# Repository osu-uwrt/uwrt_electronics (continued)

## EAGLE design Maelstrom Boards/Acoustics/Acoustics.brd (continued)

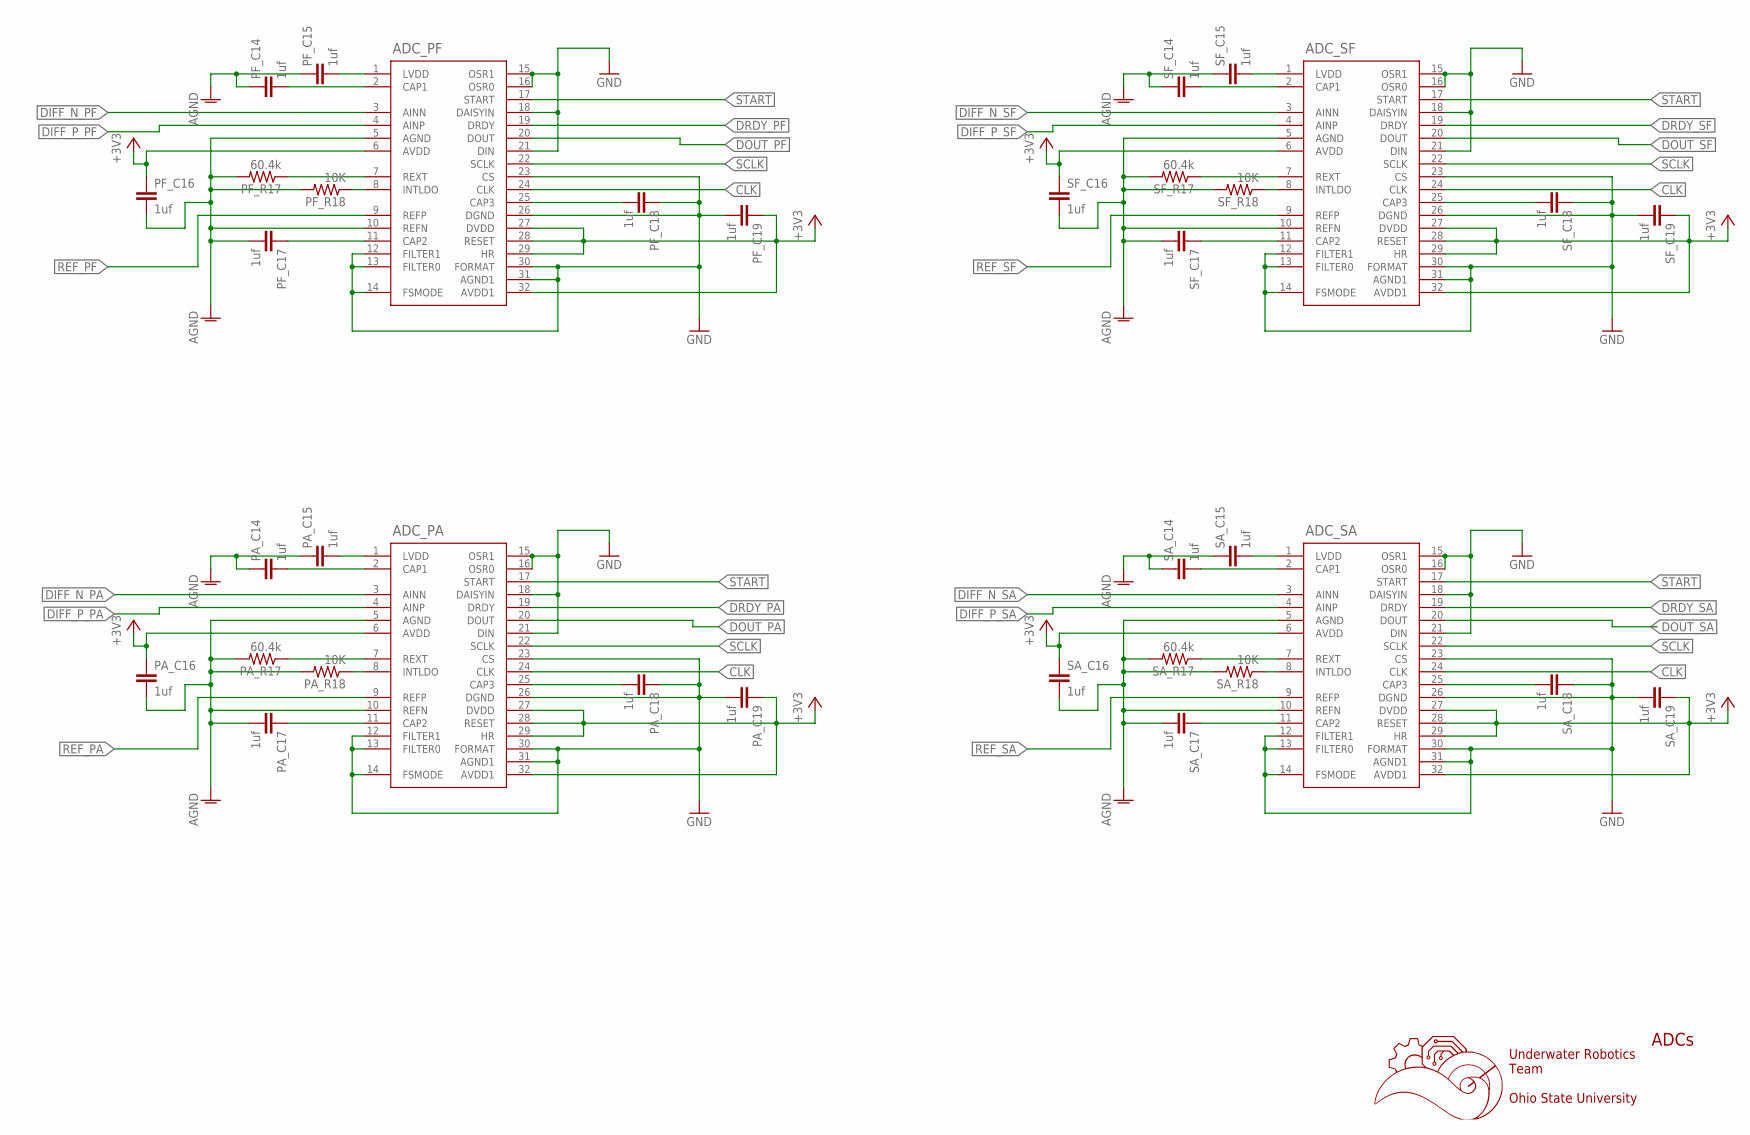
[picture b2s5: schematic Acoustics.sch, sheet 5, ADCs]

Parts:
ADC_PA: ADS124S08IPBSRPBS0032A_L; PBS0032A_L
ADC_PF: ADS124S08IPBSRPBS0032A_L; PBS0032A_L
ADC_SA: ADS124S08IPBSRPBS0032A_L; PBS0032A_L
ADC_SF: ADS124S08IPBSRPBS0032A_L; PBS0032A_L
PA_C14, PA_C15, PA_C17, PA_C18, PA_C19: 1uf; C0603
PA_C16: 1uf; C0603K
PA_R17: 60.4k; R0603
PA_R18: 10K; R0603
PF_C14, PF_C15, PF_C17, PF_C18, PF_C19: 1uf; C0603
PF_C16: 1uf; C0603K
PF_R17: 60.4k; R0603
PF_R18: 10K; R0603
SA_C14, SA_C15, SA_C17, SA_C18, SA_C19: 1uf; C0603
SA_C16: 1uf; C0603K
SA_R17: 60.4k; R0603
SA_R18: 10K; R0603
SF_C14, SF_C15, SF_C17, SF_C18, SF_C19: 1uf; C0603
SF_C16: 1uf; C0603K
SF_R17: 60.4k; R0603
SF_R18: 10K; R0603

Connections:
+3V3: ADC_PA.6 (AVDD), ADC_PA.27 (DVDD), ADC_PA.28 (RESET), ADC_PA.29 (HR), ADC_PA.32 (AVDD1), ADC_PF.6 (AVDD), ADC_PF.27 (DVDD), ADC_PF.28 (RESET), ADC_PF.29 (HR), ADC_PF.32 (AVDD1), ADC_SA.6 (AVDD), ADC_SA.27 (DVDD), ADC_SA.28 (RESET), ADC_SA.29 (HR), ADC_SA.32 (AVDD1), ADC_SF.6 (AVDD), ADC_SF.27 (DVDD), ADC_SF.28 (RESET), ADC_SF.29 (HR), ADC_SF.32 (AVDD1), PA_C16.1, PA_C19.1, PF_C16.1, PF_C19.1, SA_C16.1, SA_C19.1, SF_C16.1, SF_C19.1; also elsewhere on the board
CLK: ADC_PA.24 (CLK), ADC_PF.24 (CLK), ADC_SA.24 (CLK), ADC_SF.24 (CLK); also elsewhere on the board
DIFF_N_PA: ADC_PA.3 (AINN); also elsewhere on the board
DIFF_N_PF: ADC_PF.3 (AINN); also elsewhere on the board
DIFF_N_SA: ADC_SA.3 (AINN); also elsewhere on the board
DIFF_N_SF: ADC_SF.3 (AINN); also elsewhere on the board
DIFF_P_PA: ADC_PA.4 (AINP); also elsewhere on the board
DIFF_P_PF: ADC_PF.4 (AINP); also elsewhere on the board
DIFF_P_SA: ADC_SA.4 (AINP); also elsewhere on the board
DIFF_P_SF: ADC_SF.4 (AINP); also elsewhere on the board
DOUT_PA: ADC_PA.20 (DOUT); also elsewhere on the board
DOUT_PF: ADC_PF.20 (DOUT); also elsewhere on the board
DOUT_SA: ADC_SA.20 (DOUT); also elsewhere on the board
DOUT_SF: ADC_SF.20 (DOUT); also elsewhere on the board
DRDY_PA: ADC_PA.19 (DRDY); also elsewhere on the board
DRDY_PF: ADC_PF.19 (DRDY); also elsewhere on the board
DRDY_SA: ADC_SA.19 (DRDY); also elsewhere on the board
DRDY_SF: ADC_SF.19 (DRDY); also elsewhere on the board
GND: ADC_PA.5 (AGND), ADC_PA.10 (REFN), ADC_PA.12 (FILTER1), ADC_PA.13 (FILTER0), ADC_PA.14 (FSMODE), ADC_PA.15 (OSR1), ADC_PA.16 (OSR0), ADC_PA.18 (DAISYIN), ADC_PA.21 (DIN), ADC_PA.23 (CS), ADC_PA.26 (DGND), ADC_PA.30 (FORMAT), ADC_PA.31 (AGND1), ADC_PF.5 (AGND), ADC_PF.10 (REFN), ADC_PF.12 (FILTER1), ADC_PF.13 (FILTER0), ADC_PF.14 (FSMODE), ADC_PF.15 (OSR1), ADC_PF.16 (OSR0), ADC_PF.18 (DAISYIN), ADC_PF.21 (DIN), ADC_PF.23 (CS), ADC_PF.26 (DGND), ADC_PF.30 (FORMAT), ADC_PF.31 (AGND1), ADC_SA.5 (AGND), ADC_SA.10 (REFN), ADC_SA.12 (FILTER1), ADC_SA.13 (FILTER0), ADC_SA.14 (FSMODE), ADC_SA.15 (OSR1), ADC_SA.16 (OSR0), ADC_SA.18 (DAISYIN), ADC_SA.21 (DIN), ADC_SA.23 (CS), ADC_SA.26 (DGND), ADC_SA.30 (FORMAT), ADC_SA.31 (AGND1), ADC_SF.5 (AGND), ADC_SF.10 (REFN), ADC_SF.12 (FILTER1), ADC_SF.13 (FILTER0), ADC_SF.14 (FSMODE), ADC_SF.15 (OSR1), ADC_SF.16 (OSR0), ADC_SF.18 (DAISYIN), ADC_SF.21 (DIN), ADC_SF.23 (CS), ADC_SF.26 (DGND), ADC_SF.30 (FORMAT), ADC_SF.31 (AGND1), PA_C14.1, PA_C15.1, PA_C16.2, PA_C17.2, PA_C18.1, PA_C19.2, PA_R17.2, PA_R18.2, PF_C14.1, PF_C15.1, PF_C16.2, PF_C17.2, PF_C18.1, PF_C19.2, PF_R17.2, PF_R18.2, SA_C14.1, SA_C15.1, SA_C16.2, SA_C17.2, SA_C18.1, SA_C19.2, SA_R17.2, SA_R18.2, SF_C14.1, SF_C15.1, SF_C16.2, SF_C17.2, SF_C18.1, SF_C19.2, SF_R17.2, SF_R18.2; also elsewhere on the board
unnamed: ADC_PF.2 (CAP1), PF_C14.2
unnamed: ADC_PA.1 (LVDD), PA_C15.2
unnamed: ADC_PA.8 (INTLDO), PA_R18.1
unnamed: ADC_PA.7 (REXT), PA_R17.1
unnamed: ADC_PA.11 (CAP2), PA_C17.1
unnamed: ADC_PA.25 (CAP3), PA_C18.2
unnamed: ADC_PF.1 (LVDD), PF_C15.2
unnamed: ADC_PA.2 (CAP1), PA_C14.2
unnamed: ADC_PF.8 (INTLDO), PF_R18.1
unnamed: ADC_PF.7 (REXT), PF_R17.1
unnamed: ADC_PF.11 (CAP2), PF_C17.1
unnamed: ADC_PF.25 (CAP3), PF_C18.2
unnamed: ADC_SF.1 (LVDD), SF_C15.2
unnamed: ADC_SF.8 (INTLDO), SF_R18.1
unnamed: ADC_SF.7 (REXT), SF_R17.1
unnamed: ADC_SF.11 (CAP2), SF_C17.1
unnamed: ADC_SF.25 (CAP3), SF_C18.2
unnamed: ADC_SF.2 (CAP1), SF_C14.2
unnamed: ADC_SA.1 (LVDD), SA_C15.2
unnamed: ADC_SA.8 (INTLDO), SA_R18.1
unnamed: ADC_SA.7 (REXT), SA_R17.1
unnamed: ADC_SA.11 (CAP2), SA_C17.1
unnamed: ADC_SA.25 (CAP3), SA_C18.2
unnamed: ADC_SA.2 (CAP1), SA_C14.2
REF_PA: ADC_PA.9 (REFP); also elsewhere on the board
REF_PF: ADC_PF.9 (REFP); also elsewhere on the board
REF_SA: ADC_SA.9 (REFP); also elsewhere on the board
REF_SF: ADC_SF.9 (REFP); also elsewhere on the board
SCLK: ADC_PA.22 (SCLK), ADC_PF.22 (SCLK), ADC_SA.22 (SCLK), ADC_SF.22 (SCLK); also elsewhere on the board
START: ADC_PA.17 (START), ADC_PF.17 (START), ADC_SA.17 (START), ADC_SF.17 (START); also elsewhere on the board

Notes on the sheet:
Underwater Robotics Team Ohio State University
ADCs

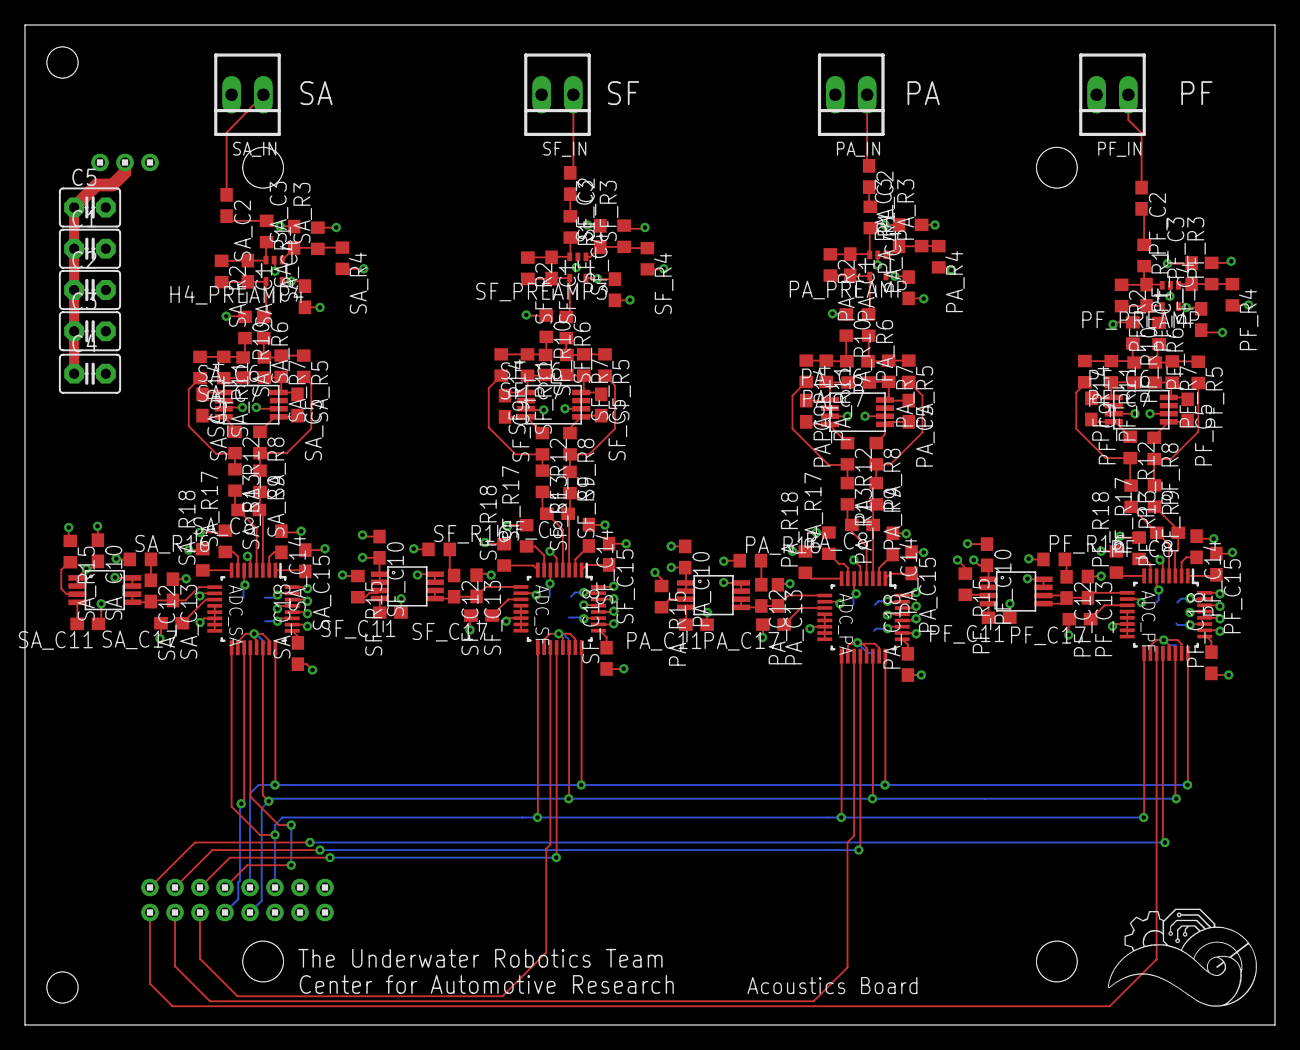
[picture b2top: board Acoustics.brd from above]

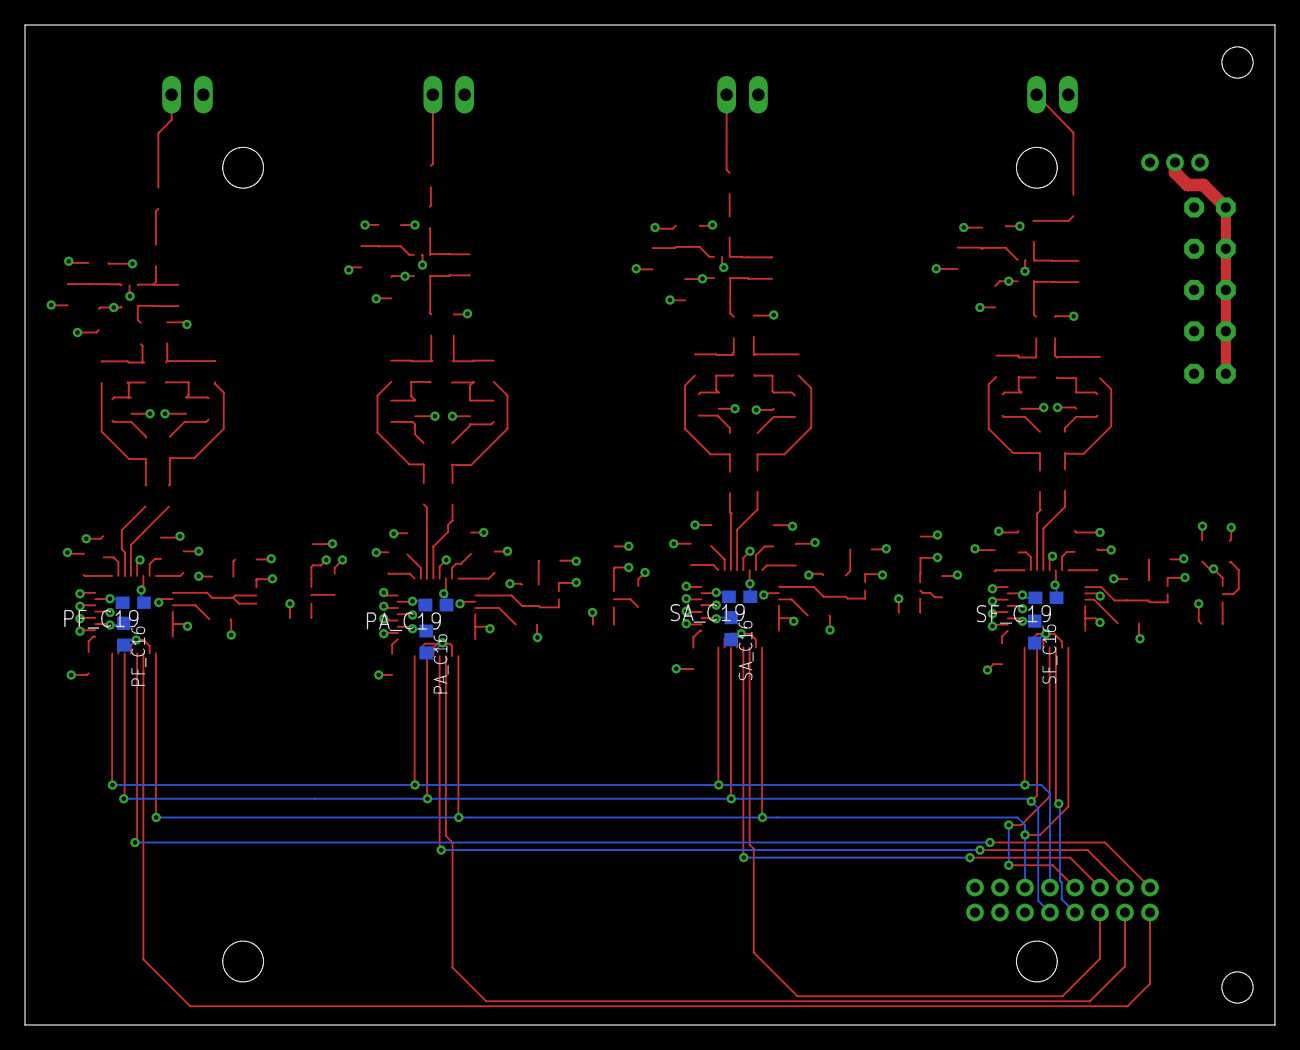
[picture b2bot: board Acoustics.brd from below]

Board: 4 copper layers, 100.0 x 80.0 mm, 175 parts (8 on the bottom side), 114 nets.

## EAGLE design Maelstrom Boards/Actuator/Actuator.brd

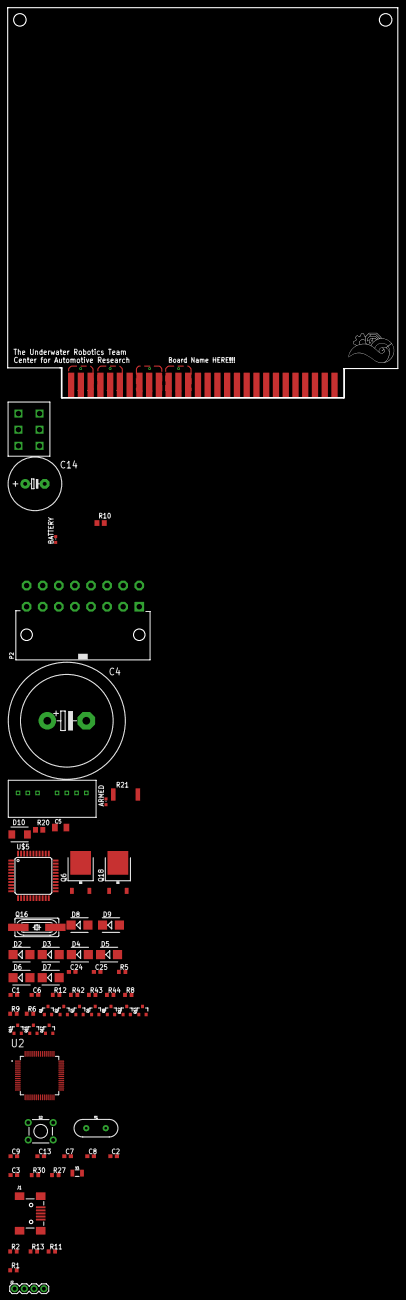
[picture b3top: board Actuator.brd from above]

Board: 2 copper layers, 101.6 x 101.6 mm, 65 parts (0 on the bottom side), 57 nets, no tracks yet.

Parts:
ARMED: CHIPLED_0603
BATTERY: CHIPLED_0603
C1, C6: 30pF; C0603
C2, C3: 18pF; C0603
C4: 22mF; EB30D
C5: 47 uF; C1206K
C7, C8: 2.2uF; C0603
C9, C13: 12.5pF; C0603
C14: 1000 uF; E5-13
C24: 220nF; C0603
C25: 100nF; C0603
D2, D3, D4, D5, D6, D7, D8, D9: SMB
D10: SMBJ
J1: USB_MINI-B_SMT; USB-MINIB
J2: 1X04
P2: 39-30-16?; 39-30-?16?
Q1, Q2, Q3, Q4, Q5, Q12, Q13, Q14, Q15, Q17: SOT23-3
Q6, Q18: TO252
Q16: HC49UP
R1, R13: 22; R0603
R2, R30: 100k; R0603
R5: 100K; R0603
R6: 5; R0603
R8, R42: 10K; R0603
R9, R12, R43, R44: 10k; R0603
R10, R20: 1.2k; R0805
R11: 560; R0603
R21: 120; R6332W
R27: 4.7k; R0603
S2: MOMENTARY-SWITCH-SPST-PTH-6.0MM; TACTILE_SWITCH_PTH_6.0MM
U2: STM32F405RGT6; QFP50P1200X1200X160-64N
U$1: 5530843-EDGE; 5530843-6-BOARDFINGERS
U$3: 6PIN-VERT; 6PIN_VERT
U$5: 18F4550; TQFP-44A-44
U$6: TMR6-2415
Y1: 12MHz; HC49US
Y3: 32.768kHz; CRYSTAL-SMD-3.2X1.5MM

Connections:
+3V3: C25.1, P2.16, R2.2, R27.2, U2.13, U2.19, U2.32, U2.48, U2.64, U$1.1, U$1.2, U$1.3, U$1.54, U$1.55, U$1.56, U$5.7, U$5.28
+5V: P2.15, U$1.11, U$1.12, U$1.13, U$1.44, U$1.45, U$1.46
+12V: D8.C, D9.C, P2.9
+24V: C4.+, D2.C, D3.C, D4.C, D5.C, D6.C, D7.C, D10.C, Q6.2, Q18.2, R5.1, R9.2, R20.2, R21.2, R43.2
AGND: ARMED.C, BATTERY.C, C1.2, C2.2, C3.2, C4.-, C5.2, C6.2, C7.1, C8.1, C9.2, C13.2, C14.-, C24.2, C25.2, D10.A, J1.GND, P2.2, Q1.2, Q2.2, Q3.2, Q4.2, Q5.2, Q12.2, Q13.2, Q14.2, Q15.2, Q17.2, R8.2, R30.2, R42.2, S2.1, U2.12, U2.18, U2.63, U$1.4, U$1.5, U$1.6, U$1.8, U$1.9, U$1.10, U$1.47, U$1.48, U$1.49, U$1.51, U$1.52, U$1.53, U$3.1-, U$3.2-, U$3.3-, U$5.6, U$5.29, U$6.P$1, U$6.P$7
ARM_TORPEDO: U2.39, U$5.10, U$6.P$3
COIL_1: D5.A, P2.8, Q4.3
COIL_1_GATE: Q4.1, U2.61, U$5.38
COIL_2: D7.A, P2.7, Q14.3
COIL_2_GATE: Q14.1, U2.62, U$5.39
COIL_3: D3.A, P2.6, Q5.3
COIL_3_GATE: Q5.1, U2.29, U$5.40
COIL_4: D4.A, P2.5, Q13.3
COIL_4_GATE: Q13.1, U2.30, U$5.41
COIL_5: D6.A, P2.4, Q15.3
COIL_5_GATE: Q15.1, U2.33, U$5.2
COIL_S: D2.A, P2.3, Q1.3
COIL_S_GATE: Q1.1, U2.34, U$5.3
DROPPER1: D8.A, P2.10, Q17.3
DROPPER1_GATE: Q17.1, U2.35, U$5.4
DROPPER2: D9.A, P2.11, Q12.3
DROPPER2_GATE: Q12.1, U2.36, U$5.5
unnamed: C2.1, U2.6, Y1.1
unnamed: C3.1, U2.5, Y1.2
unnamed: C8.2, U2.47
unnamed: R5.2, R8.1, U$5.19
unnamed: C13.1, U2.4, Y3.P$1
unnamed: J1.ID, R11.1
unnamed: J1.D+, R1.1
unnamed: J1.D-, R13.1
unnamed: BATTERY.A, R10.1
unnamed: ARMED.A, R20.1
unnamed: C7.2, U2.31
unnamed: Q2.3, R44.1
unnamed: Q18.1, R43.1, R44.2
unnamed: C6.1, Q16.2, U$5.31
unnamed: C1.1, Q16.1, U$5.30
unnamed: R6.1, U$5.23
unnamed: Q6.1, R9.1, R12.2
unnamed: C5.1, R21.1, U$6.P$6
unnamed: Q3.3, R12.1
unnamed: C9.1, U2.3, Y3.P$2
unnamed: R30.1, U2.60
unnamed: C24.1, U$5.37
unnamed: R42.1, U$5.15
unnamed: R27.1, S2.3, U2.7
PWM_CLAW: P2.1, U2.14
SCL: U2.58, U$1.31, U$5.9
SDA: U2.59, U$1.32, U$5.8
TORPEDO1: P2.14, Q18.3
TORPEDO1_GATE: Q2.1, U2.37, U$5.11
TORPEDO2: P2.13, Q6.3
TORPEDO2_GATE: Q3.1, U2.38, U$5.14
USB_DN: R13.2, U2.44
USB_DP: R1.2, U2.45
USB_ID: R2.1, R11.2
V+: C14.+, R10.2, U$3.1+, U$3.2+, U$3.3+, U$6.P$2

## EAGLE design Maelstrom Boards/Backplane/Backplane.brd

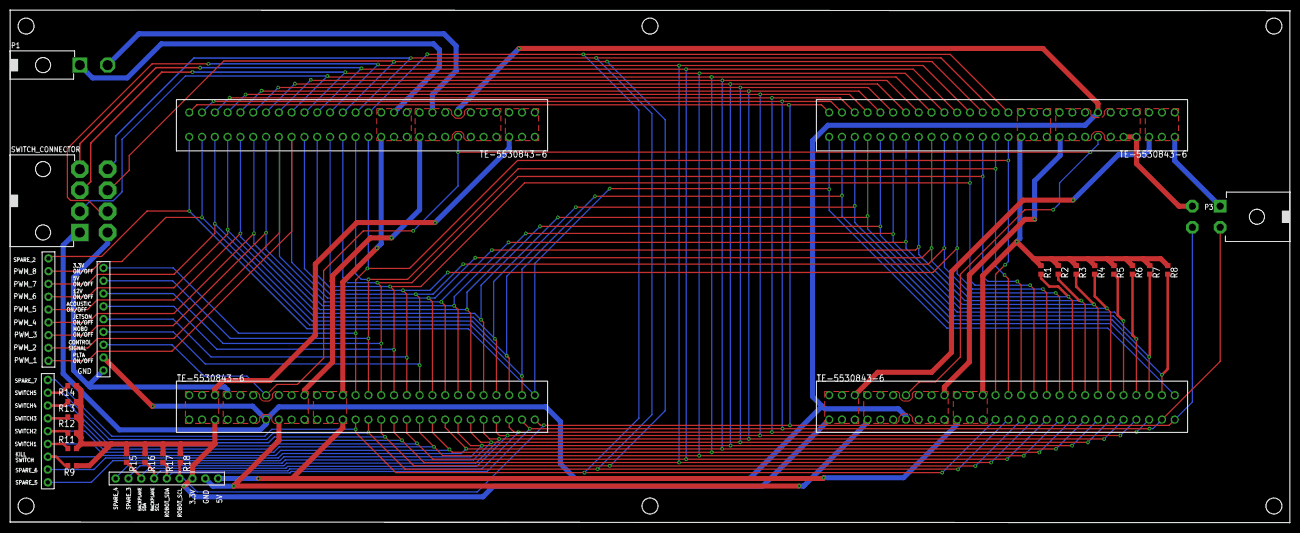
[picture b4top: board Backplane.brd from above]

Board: 2 copper layers, 254.0 x 101.7 mm, 29 parts (0 on the bottom side), 35 nets.

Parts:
P1: 39-30-02?_S; 39-30-?02?
P3: 39-30-04?_S; 39-30-?04?
R1, R2, R3, R4, R5, R6, R7, R8, R9, R10, R11, R12, R13, R14: 10k; R0603
R15, R16, R17, R18: 4.7k; R0603
SWITCH_CONNECTOR: 39-30-08?_S; 39-30-?08?
U$1, U$2, U$3, U$4: 5530843-FEMALE; 5530843-6-BACKPLANEMATE
U$5: 929870-01-09_1; 929852-01-09_1ROW
U$6: 929870-01-09_2; 929852-01-09_1ROW
U$7: 929870-01-09_3; 929852-01-09_1ROW
U$8: 929870-01-09_4; 929852-01-09_1ROW

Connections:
3.3V: P3.1, R9.1, R10.1, R11.1, R12.1, R13.1, R14.1, R15.1, R16.1, R17.1, R18.1, U$1.1, U$1.2, U$1.3, U$1.54, U$1.55, U$1.56, U$2.1, U$2.2, U$2.3, U$2.54, U$2.55, U$2.56, U$3.1, U$3.2, U$3.3, U$3.54, U$3.55, U$3.56, U$4.1, U$4.2, U$4.3, U$4.54, U$4.55, U$4.56, U$8.P$7
3.3V_ON/OFF: U$1.14, U$2.14, U$3.14, U$4.14, U$7.P$1
5V: P1.1, R1.1, R2.1, R3.1, R4.1, R5.1, R6.1, R7.1, R8.1, U$1.11, U$1.12, U$1.13, U$1.44, U$1.45, U$1.46, U$2.11, U$2.12, U$2.13, U$2.44, U$2.45, U$2.46, U$3.11, U$3.12, U$3.13, U$3.44, U$3.45, U$3.46, U$4.11, U$4.12, U$4.13, U$4.44, U$4.45, U$4.46, U$8.P$9
5V_ON/OFF: U$1.15, U$2.15, U$3.15, U$4.15, U$7.P$2
12V_ON/OFF: U$1.16, U$2.16, U$3.16, U$4.16, U$7.P$3
ACOUSTIC_ON/OFF: U$1.17, U$2.17, U$3.17, U$4.17, U$7.P$4
BACKPLANE_SCL: R16.2, U$1.31, U$2.31, U$3.31, U$4.31, U$8.P$4
BACKPLANE_SDA: R15.2, U$1.32, U$2.32, U$3.32, U$4.32, U$8.P$3
CONTROL_SIGNAL: U$1.7, U$2.7, U$3.7, U$4.7, U$7.P$7
GND: P1.2, P3.3, SWITCH_CONNECTOR.5, U$1.4, U$1.5, U$1.6, U$1.8, U$1.9, U$1.10, U$1.47, U$1.48, U$1.49, U$1.51, U$1.52, U$1.53, U$2.4, U$2.5, U$2.6, U$2.8, U$2.9, U$2.10, U$2.47, U$2.48, U$2.49, U$2.51, U$2.52, U$2.53, U$3.4, U$3.5, U$3.6, U$3.8, U$3.9, U$3.10, U$3.47, U$3.48, U$3.49, U$3.51, U$3.52, U$3.53, U$4.4, U$4.5, U$4.6, U$4.8, U$4.9, U$4.10, U$4.47, U$4.48, U$4.49, U$4.51, U$4.52, U$4.53, U$7.P$9, U$8.P$8
JETSON_ON/OFF: U$1.18, U$2.18, U$3.18, U$4.18, U$7.P$5
KILL_SWITCH: R9.2, SWITCH_CONNECTOR.2, U$1.37, U$2.37, U$3.37, U$4.37, U$5.P$7
MOBO_ON/OFF: U$1.19, U$2.19, U$3.19, U$4.19, U$7.P$6
PLTA_ON/OFF: SWITCH_CONNECTOR.1, U$1.50, U$2.50, U$3.50, U$4.50, U$7.P$8
PWM_1: R1.2, U$1.20, U$2.20, U$3.20, U$4.20, U$6.P$9
PWM_2: R2.2, U$1.21, U$2.21, U$3.21, U$4.21, U$6.P$8
PWM_3: R3.2, U$1.22, U$2.22, U$3.22, U$4.22, U$6.P$7
PWM_4: R4.2, U$1.23, U$2.23, U$3.23, U$4.23, U$6.P$6
PWM_5: R5.2, U$1.24, U$2.24, U$3.24, U$4.24, U$6.P$5
PWM_6: R6.2, U$1.25, U$2.25, U$3.25, U$4.25, U$6.P$4
PWM_7: R7.2, U$1.26, U$2.26, U$3.26, U$4.26, U$6.P$3
PWM_8: R8.2, U$1.27, U$2.27, U$3.27, U$4.27, U$6.P$2
ROBOT_SCL: P3.4, R18.2, U$1.29, U$2.29, U$3.29, U$4.29, U$8.P$6
ROBOT_SDA: P3.2, R17.2, U$1.30, U$2.30, U$3.30, U$4.30, U$8.P$5
SPARE2: U$1.28, U$2.28, U$3.28, U$4.28, U$6.P$1
SPARE3: U$1.33, U$2.33, U$3.33, U$4.33, U$8.P$2
SPARE4: U$1.34, U$2.34, U$3.34, U$4.34, U$8.P$1
SPARE5: U$1.35, U$2.35, U$3.35, U$4.35, U$5.P$9
SPARE6: U$1.36, U$2.36, U$3.36, U$4.36, U$5.P$8
SPARE7: U$1.43, U$2.43, U$3.43, U$4.43, U$5.P$1
SWITCH_1: R10.2, SWITCH_CONNECTOR.3, U$1.38, U$2.38, U$3.38, U$4.38, U$5.P$6
SWITCH_2: R11.2, SWITCH_CONNECTOR.4, U$1.39, U$2.39, U$3.39, U$4.39, U$5.P$5
SWITCH_3: R12.2, SWITCH_CONNECTOR.6, U$1.40, U$2.40, U$3.40, U$4.40, U$5.P$4
SWITCH_4: R13.2, SWITCH_CONNECTOR.7, U$1.41, U$2.41, U$3.41, U$4.41, U$5.P$3
SWITCH_5: R14.2, SWITCH_CONNECTOR.8, U$1.42, U$2.42, U$3.42, U$4.42, U$5.P$2

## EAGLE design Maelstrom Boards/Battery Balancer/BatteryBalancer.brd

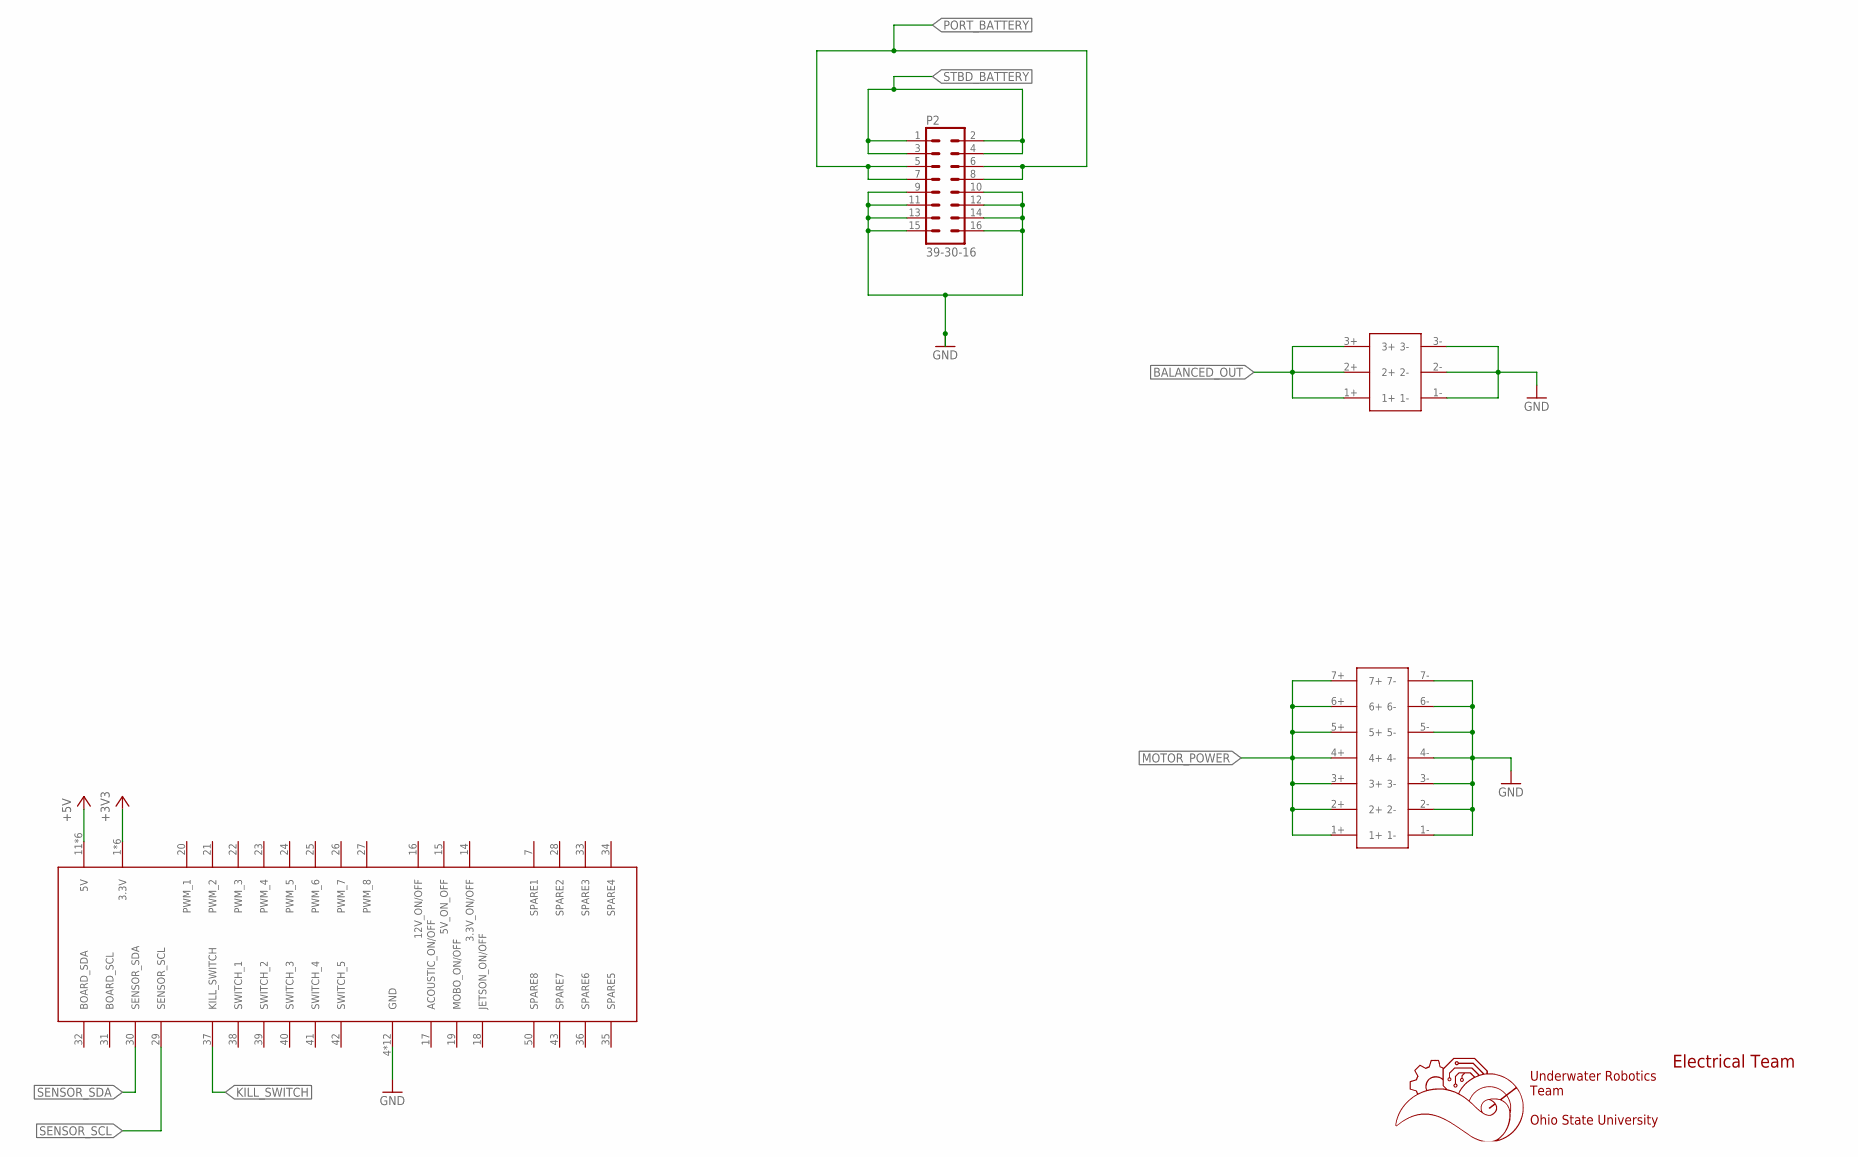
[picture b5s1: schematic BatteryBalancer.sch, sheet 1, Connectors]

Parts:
P2: 39-30-16; 39-30-?16?
U$1: 5530843-EDGE; 5530843-6-BOARDFINGERS
U$4: 14PIN-VERT; 14PIN_VERT
U$13: 6PIN-VERT; 6PIN_VERT

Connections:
+3V3: U$1.1 (3.3V), U$1.2 (3.3V), U$1.3 (3.3V), U$1.54 (3.3V), U$1.55 (3.3V), U$1.56 (3.3V); also elsewhere on the board
+5V: U$1.11 (5V), U$1.12 (5V), U$1.13 (5V), U$1.44 (5V), U$1.45 (5V), U$1.46 (5V)
BALANCED_OUT: U$13.1+, U$13.2+, U$13.3+; also elsewhere on the board
GND: P2.9, P2.10, P2.11, P2.12, P2.13, P2.14, P2.15, P2.16, U$1.4 (GND), U$1.5 (GND), U$1.6 (GND), U$1.8 (GND), U$1.9 (GND), U$1.10 (GND), U$1.47 (GND), U$1.48 (GND), U$1.49 (GND), U$1.51 (GND), U$1.52 (GND), U$1.53 (GND), U$4.1-, U$4.2-, U$4.3-, U$4.4-, U$4.5-, U$4.6-, U$4.7-, U$13.1-, U$13.2-, U$13.3-; also elsewhere on the board
KILL_SWITCH: U$1.37 (KILL_SWITCH); also elsewhere on the board
MOTOR_POWER: U$4.1+, U$4.2+, U$4.3+, U$4.4+, U$4.5+, U$4.6+, U$4.7+; also elsewhere on the board
PORT_BATTERY: P2.5, P2.6, P2.7, P2.8; also elsewhere on the board
SENSOR_SCL: U$1.29 (SENSOR_SCL); also elsewhere on the board
SENSOR_SDA: U$1.30 (SENSOR_SDA); also elsewhere on the board
STBD_BATTERY: P2.1, P2.2, P2.3, P2.4; also elsewhere on the board

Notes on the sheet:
Underwater Robotics Team Ohio State University
Electrical Team

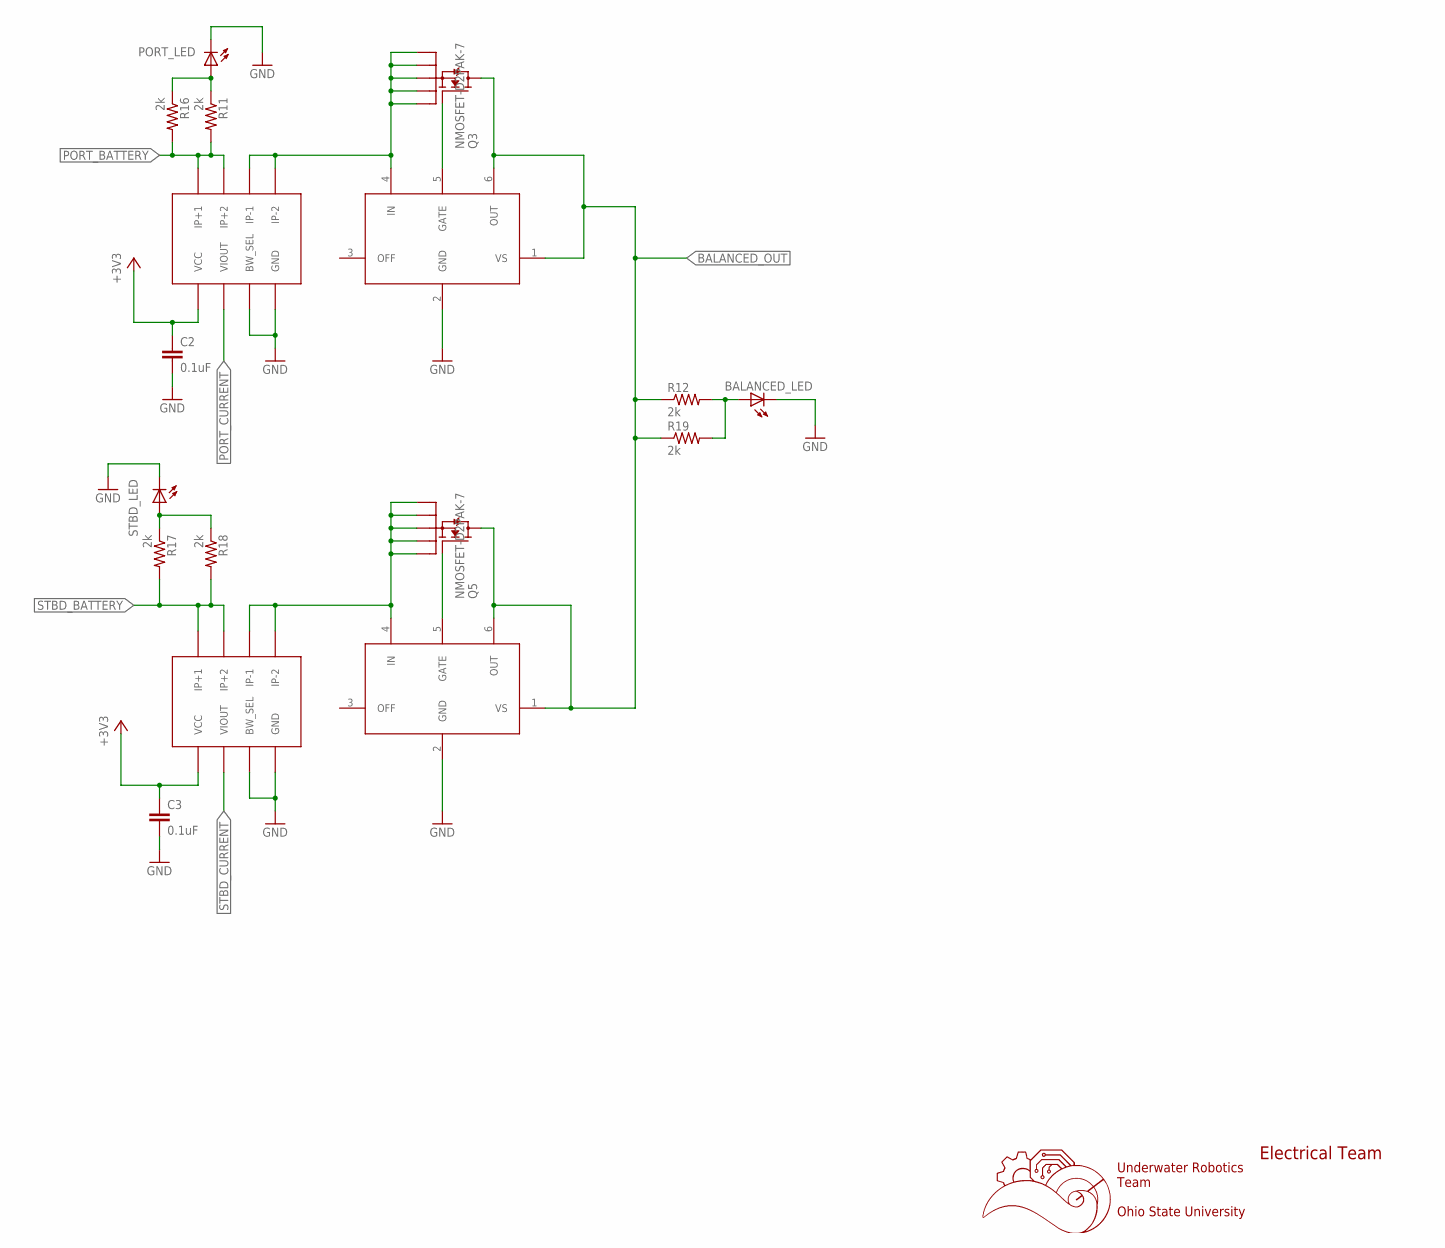
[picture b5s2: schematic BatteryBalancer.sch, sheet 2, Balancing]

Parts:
BALANCED_LED: LEDCHIP-LED0603; CHIP-LED0603
C2, C3: 0.1uF; C0603
PORT_LED: LEDCHIP-LED0603; CHIP-LED0603
Q3, Q5: NMOSFET-D2PAK-7; D2PAK-7
R11, R12, R16, R17, R18, R19: 2k; R0603
STBD_LED: LEDCHIP-LED0603; CHIP-LED0603
U$2, U$3: LM5050
U$6, U$7: ACS722; SOIC-8

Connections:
+3V3: C2.1, C3.1, U$6.VCC, U$7.VCC; also elsewhere on the board
BALANCED_OUT: Q3.D, Q5.D, R12.1, R19.1, U$2.1 (VS), U$2.6 (OUT), U$3.1 (VS), U$3.6 (OUT); also elsewhere on the board
GND: BALANCED_LED.C, C2.2, C3.2, PORT_LED.C, STBD_LED.C, U$2.2 (GND), U$3.2 (GND), U$6.BW_SEL, U$6.GND, U$7.BW_SEL, U$7.GND; also elsewhere on the board
unnamed: Q3.S1, Q3.S2, Q3.S3, Q3.S4, Q3.S5, U$2.4 (IN), U$6.IP-1, U$6.IP-2
unnamed: Q3.G, U$2.5 (GATE)
unnamed: Q5.G, U$3.5 (GATE)
unnamed: PORT_LED.A, R11.1, R16.1
unnamed: R17.1, R18.1, STBD_LED.A
unnamed: BALANCED_LED.A, R12.2, R19.2
PORT_BATTERY: R11.2, R16.2, U$6.IP+1, U$6.IP+2; also elsewhere on the board
PORT_CURRENT: U$6.VIOUT; also elsewhere on the board
SOURCE: Q5.S1, Q5.S2, Q5.S3, Q5.S4, Q5.S5, U$3.4 (IN), U$7.IP-1, U$7.IP-2
STBD_BATTERY: R17.2, R18.2, U$7.IP+1, U$7.IP+2; also elsewhere on the board
STBD_CURRENT: U$7.VIOUT; also elsewhere on the board

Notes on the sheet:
Underwater Robotics Team Ohio State University
Electrical Team

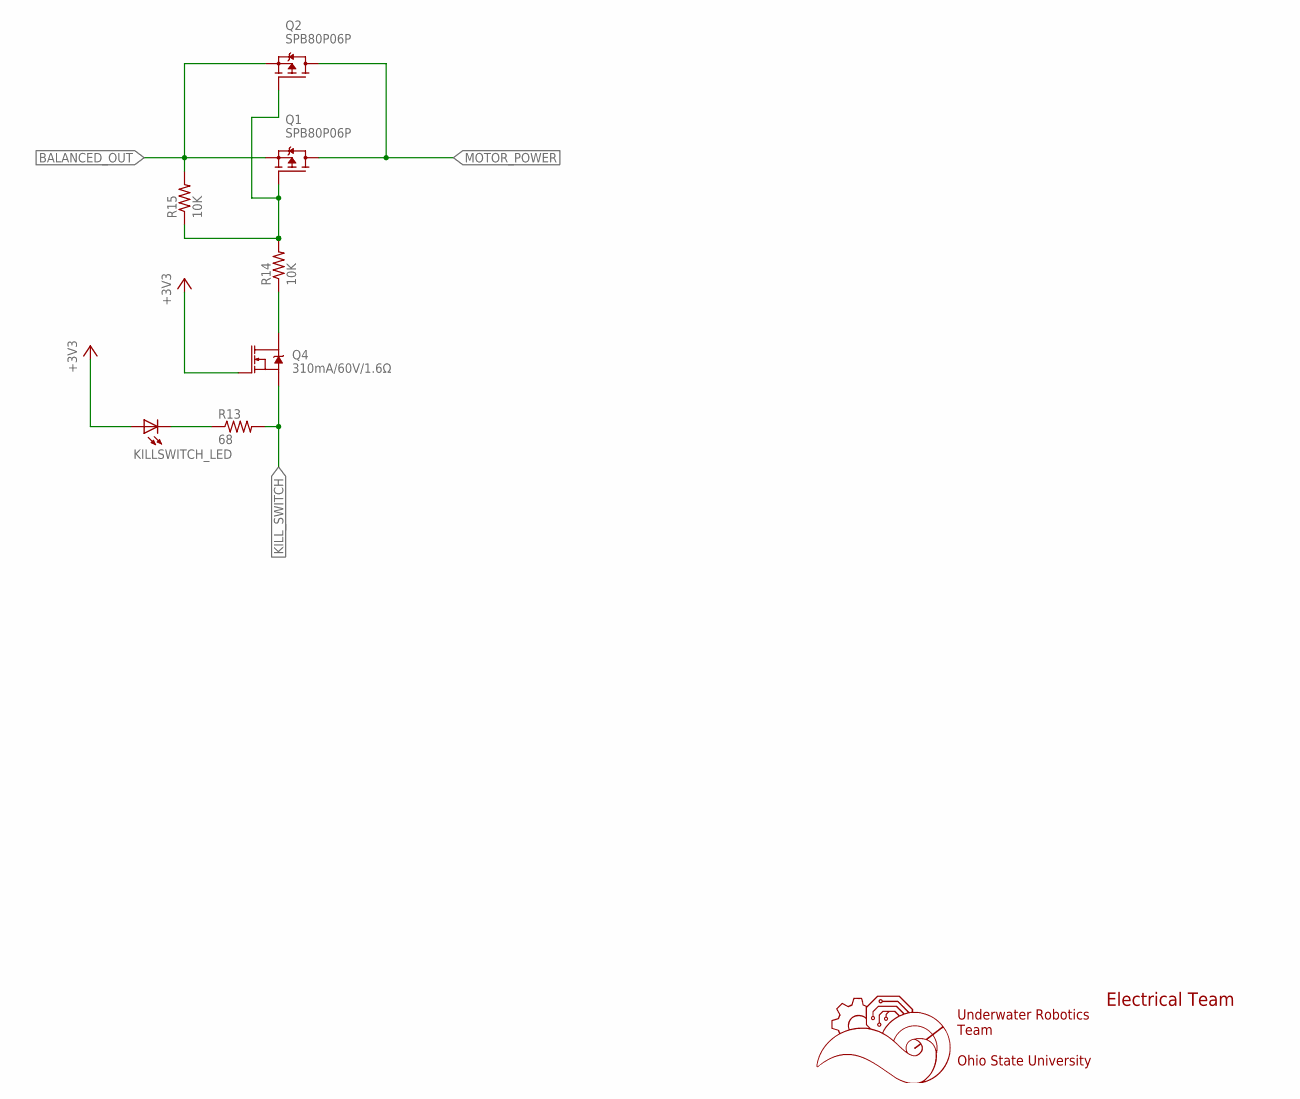
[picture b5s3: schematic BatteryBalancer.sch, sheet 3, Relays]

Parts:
KILLSWITCH_LED: LEDCHIP-LED0603; CHIP-LED0603
Q1, Q2: SPB80P06P; TO263
Q4: 310mA/60V/1.6Ω; SOT323
R13: 68; R0603
R14, R15: 10K; R0603

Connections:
+3V3: KILLSWITCH_LED.A, Q4.1 (G); also elsewhere on the board
BALANCED_OUT: Q1.2 (S), Q2.2 (S), R15.2; also elsewhere on the board
KILL_SWITCH: Q4.2 (S), R13.2; also elsewhere on the board
MOTOR_POWER: Q1.3 (D), Q2.3 (D); also elsewhere on the board
unnamed: Q4.3 (D), R14.1
unnamed: Q1.1 (G), Q2.1 (G), R14.2, R15.1
unnamed: KILLSWITCH_LED.C, R13.1

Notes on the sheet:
Underwater Robotics Team Ohio State University
Electrical Team

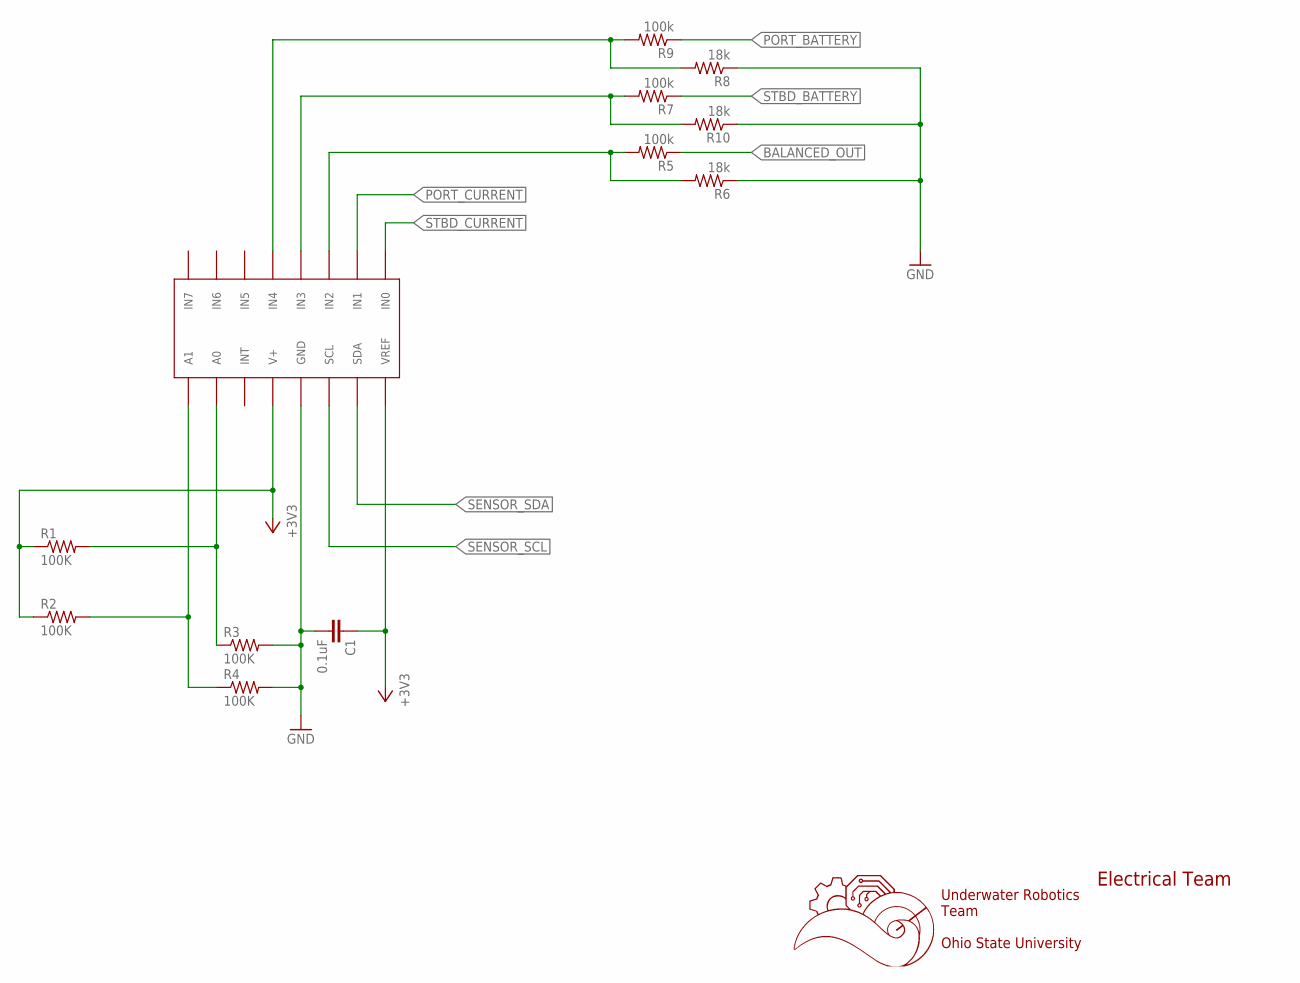
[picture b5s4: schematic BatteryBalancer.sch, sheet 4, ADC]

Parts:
C1: 0.1uF; C0603
R1, R2, R3, R4: 100K; R0603
R5, R7, R9: 100k; R0603
R6, R8, R10: 18k; R0603
U$12: ADC128D818; TSSOP-16

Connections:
+3V3: C1.1, R1.1, R2.1, U$12.V+, U$12.VREF; also elsewhere on the board
BALANCED_OUT: R5.1; also elsewhere on the board
GND: C1.2, R3.2, R4.2, R6.1, R8.1, R10.1, U$12.GND; also elsewhere on the board
unnamed: R2.2, R4.1, U$12.A1
unnamed: R1.2, R3.1, U$12.A0
unnamed: R7.2, R10.2, U$12.IN3
unnamed: R8.2, R9.2, U$12.IN4
unnamed: R5.2, R6.2, U$12.IN2
PORT_BATTERY: R9.1; also elsewhere on the board
PORT_CURRENT: U$12.IN1; also elsewhere on the board
SENSOR_SCL: U$12.SCL; also elsewhere on the board
SENSOR_SDA: U$12.SDA; also elsewhere on the board
STBD_BATTERY: R7.1; also elsewhere on the board
STBD_CURRENT: U$12.IN0; also elsewhere on the board

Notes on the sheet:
Underwater Robotics Team Ohio State University
Electrical Team
